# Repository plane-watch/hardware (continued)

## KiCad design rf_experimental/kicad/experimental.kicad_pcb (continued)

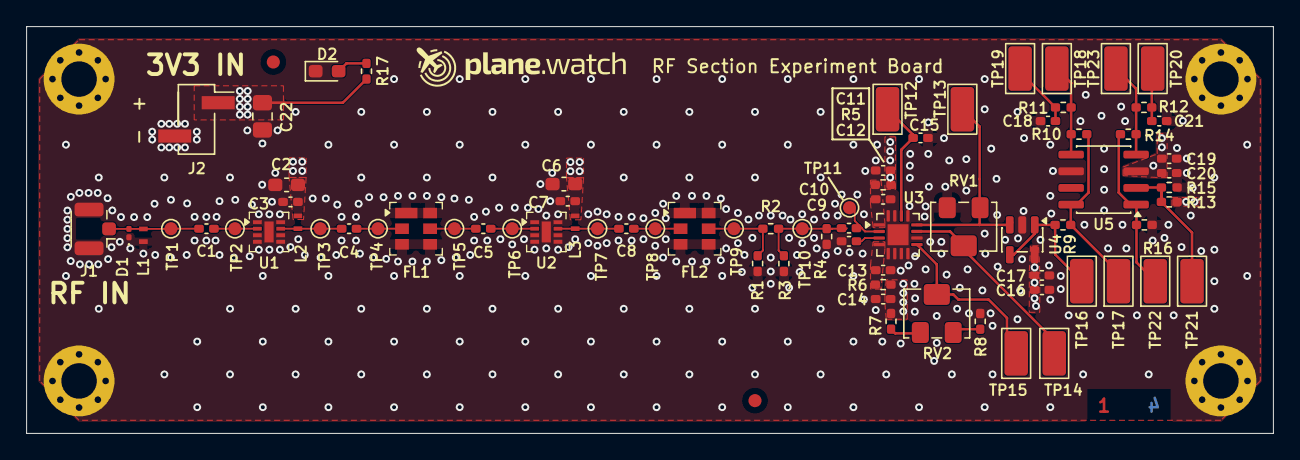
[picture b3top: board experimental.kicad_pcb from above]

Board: 4 copper layers, 95.0 x 31.0 mm, 85 parts (0 on the bottom side), 31 nets.

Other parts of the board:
Layer_Window: LayerMarker_4_6.35x2.54mm_TextH1mm_P1.27mm_LowerM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; LayerMarker_4_6.35x2.54mm_TextH1mm_P1.27mm_LowerMirrored

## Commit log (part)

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2026-04-21 reorg
2026-04-21 add comment
2026-05-02 add FPGA datasheet & pinout
2026-05-02 add LT8640 symbol
2026-05-02 add TI TPS2296xC symbol
2026-05-02 FPGA Power, FPGA data headers & series R, clean up
2026-05-03 fix errors
    - fix text in LT8640 symbol
    - fix missing net name on ADC input driver tage
2026-05-03 Add footprint: L_Coilcraft_0402DC_1005Metric
2026-05-03 tidy up, better symbols, add footprints
2026-05-05 add datasheets for parts used
2026-05-05 add solder paste window pane calculator spreadsheet
2026-05-05 add pcbway stackup info & impedance calcs
2026-05-05 work on layout
2026-05-05 Updates after screen share
2026-05-05 Remove lock file
2026-05-08 swap ADC to AD9003 + schematic updates
2026-05-08 work on board layout
2026-05-09 finish first rev pcb
2026-05-09 update groups
2026-05-09 MOAR VIAS
2026-05-10 work on silk screening
2026-05-10 work on silkscreen & vias under regulators
2026-05-10 minor updates while reviewing
2026-05-11 add jumpers for testing different power rails & additional test point
2026-05-11 address & fix ERC errors/warnings
2026-05-11 fix all ERC & DRCC errors & warnings
2026-05-11 adjust logo spacing
2026-05-11 tidy up vias
2026-05-11 add test point for ADC VREF
2026-05-13 updates before fab
2026-05-13 fix via positioning
2026-05-13 review BoM
2026-05-13 mark RF shield as do not populate for prototype
2026-05-13 change AD8138 feedback resistor network in-line with datasheet
2026-05-13 work on documentation
2026-05-15 rationalise power to single 3V3 rail fed from FPGA VCC
2026-05-15 bump version to proto 1.1
2026-05-15 add workflow to run ERC & DRC
2026-05-16 add kicadiff action
2026-05-16 troubleshoot kicadiff
2026-05-16 troubleshoot actions
2026-05-16 update date
2026-05-16 make AD8318 +OUT/-OUT test pads symmetric and minimal
    now as close to the pins as possible while maintaining clearances and guarded with via fencing
2026-05-16 adjust silkscreen to ensure no overlap & adhere to clearances
2026-05-16 add date to pcb
2026-05-16 more vias because i have a mental problem
2026-05-16 fix R43 metadata
2026-05-16 work on github action
2026-05-16 update corner keep-out zones to only include fills
2026-05-16 Add LDO PG pin to FPGA for monitoring in SW. Add Blinkenlights.
2026-05-16 Add voltage divider to PGFB to assert PG if 3V3 > ~3.1V. Fix length of AINN net.
2026-05-16 move vias
2026-05-16 Add persistent PCBWay BOM fields to KiCad schematic
2026-05-17 add 3d models for nicer render
2026-05-17 initial readme
2026-05-17 work on readme
2026-05-17 work on readme, add license
2026-05-17 legal mumbo jumbo
2026-05-17 remove kinotes
2026-05-17 move readme to repo root
2026-05-17 resolve "Missing symbol field 'Package' in footprint" DRC errors
2026-05-17 replace manual layer markers with footprint
2026-05-18 move power supply and add GPS module
2026-05-18 fix incorrect part number
2026-05-18 fix LED order
2026-05-18 review & consolidate all capacitors
2026-05-19 review & consolidate all resistors
2026-05-19 update inductor datasheet
2026-05-19 sync pcb fields from sch
2026-05-19 add item to todo list
2026-05-19 swap TVS diodes with easier to source part
2026-05-19 add license & copyright info to schematic and pcb. fix layer window.
2026-05-19 update render
2026-05-19 DRC fixes
2026-05-20 added lcsc_ids to all parts
2026-05-20 update stackup for "JLC04161H-7628" and adjust impedance controlled traces
2026-05-20 fix wrong date on silk
2026-05-20 adjust RF netclass and material labels
2026-05-20 change discontinued parts
2026-05-20 update BoM to available parts from LCSC
2026-05-20 add pink led for gps pps + attach gps reset to fpga
2026-05-20 fix drc by syncing fields
2026-05-20 add missing 3D model
2026-05-20 update render foor readme
2026-05-20 better footprint for log detector
2026-05-20 update render for readme
2026-05-20 correct 3d model for LT3045
2026-05-20 update mask colour in line with what's been ordered
2026-06-04 first draft of bring-up plan
2026-06-10 Add RF experiment board
2026-06-17 Change ADC gain/feedback network resistors to higher value
    - We were overloading the output of the ADL5513, with gain/feedback resistors with resistance too low.
    - Change R37, R38, R39 and R40 values from 499Ω to 4.7kΩ
2026-06-17 Add footprints for ADL5513 slope adjustment and output filtering
    - Add R44 (0Ω) & R45 (DNP, footprint only), allowing for replacement to adjust slope.
    - Add C61 (DNP, footprint only), allowing for output filtering to reduce output bandwidth if needed.
2026-06-18 Add datasheets for bias tee power switch & gps module
2026-06-18 Add bias-tee power switch & connect GPS TP2
2026-06-18 Decrease brightness of PPS LED
    Bump up series resistor to 1kΩ from 58Ω (lol)
2026-06-19 Swap the SMA connectors for U.FL
2026-06-19 Add optional PPS output
2026-06-19 Tidy up
2026-06-19 Update PCB to include PPS output
2026-06-19 Add 3D model for TVS diode
2026-06-21 Add footprints for ADC driver feedback capacitors
    Cf in datasheet, figure 42.
2026-06-21 Implement log detector output buffering & buffered low-pass filter for noise offset
    - Implement low-pass filter to output noise floor with no pulses
    - Feed noise floor into ADC driver -IN to improve range/sensitivity
    - Buffer low pass filter output
    - Buffer log detector output with spare op amp in OPA2320 package
    - Tidy schematic & vias
2026-06-21 Make hand soldered pads thermal relief
2026-06-21 Update BoM
2026-06-21 Schematic annotations
2026-06-22 Move U.FL connectors in as far as possible
2026-06-22 Replace TADJ prototype trimmer with voltage divider
    Voltage divider sets the ADL5513 TADJ pin to approximately 0.85 V for 1090 MHz operation
2026-06-22 Mark impedance controlled traces as "RF_50Ω" in schematic
2026-06-22 Update impedance controlled trace width following feedback from JLCPCB
    net class "RF_50Ω" now 0.34544mm trace width.
2026-06-23 Add animated GIF
2026-06-24 add dependabot
2026-06-24 fix dependabot
2026-06-24 Bump sksat/kicadiff from 0.1.1 to 0.2.0
    Bumps [sksat/kicadiff](https://github.com/sksat/kicadiff) from 0.1.1 to 0.2.0.
    - [Release notes](https://github.com/sksat/kicadiff/releases)
    - [Changelog](https://github.com/sksat/kicadiff/blob/main/CHANGELOG.md)
    - [Commits](https://github.com/sksat/kicadiff/compare/v0.1.1...v0.2.0)
    ---
    updated-dependencies:
2026-06-24 Bump actions/checkout from 6 to 7
    Bumps [actions/checkout](https://github.com/actions/checkout) from 6 to 7.
    - [Release notes](https://github.com/actions/checkout/releases)
    - [Changelog](https://github.com/actions/checkout/blob/main/CHANGELOG.md)
    - [Commits](https://github.com/actions/checkout/compare/v6...v7)
    ---
    updated-dependencies:
2026-06-24 Add marked up image of PCB
2026-06-27 add rf stage measurements
2026-06-27 add rf stage measurements for proto 1.2
2026-06-29 Replace AD8138 gain/feedback resistors with resistor array
    R37, R38, R39, R40 -> RN1.
    Resolves: https://github.com/plane-watch/hardware/pull/5#issuecomment-4815513095
2026-06-29 Add optional 2-section input LC matching/filter network
    Default: series 0R, shunts DNP.
    Populate after VNA/S11 testing to compensate ESD/bias-tee/LNA input parasitics.
2026-06-29 Add RF frontend tuning footprints
    Add DNP RF tuning footprints around the input match, SAW filter ports, and
    log detector input path. Update schematic annotations for VNA-populated C/L/R
    matching options, mark AD8138 feedback caps as optional, and update the PCB
    layout for the new RF frontend tuning network.
2026-06-29 Change all test point footprints to TestPoint_THTPad_D1.0mm_Drill0.5mm
    Had to move TP15 slightly to prevent it shorting to 3V3.
2026-06-29 Update LED series resistors with resistor arrays
    Also remove thermal vias - Shorty has a board heater now :)
2026-06-29 Update land pattern for ESD diodes to match mfr datasheet
2026-06-29 Update R40 description
2026-06-29 Update purpose fields with more descriptive text for future me
2026-06-29 Metadata updates to match schematic
2026-06-29 Update issue date on drawings
2026-06-30 Slow down the LPF to avoid artificially raising the noise-floor baseline in high traffic areas
2026-06-30 Add RF short to ground on bias-tee supply
2026-06-30 Move C67 closer to L12
2026-06-30 Tighten up RF section layout
